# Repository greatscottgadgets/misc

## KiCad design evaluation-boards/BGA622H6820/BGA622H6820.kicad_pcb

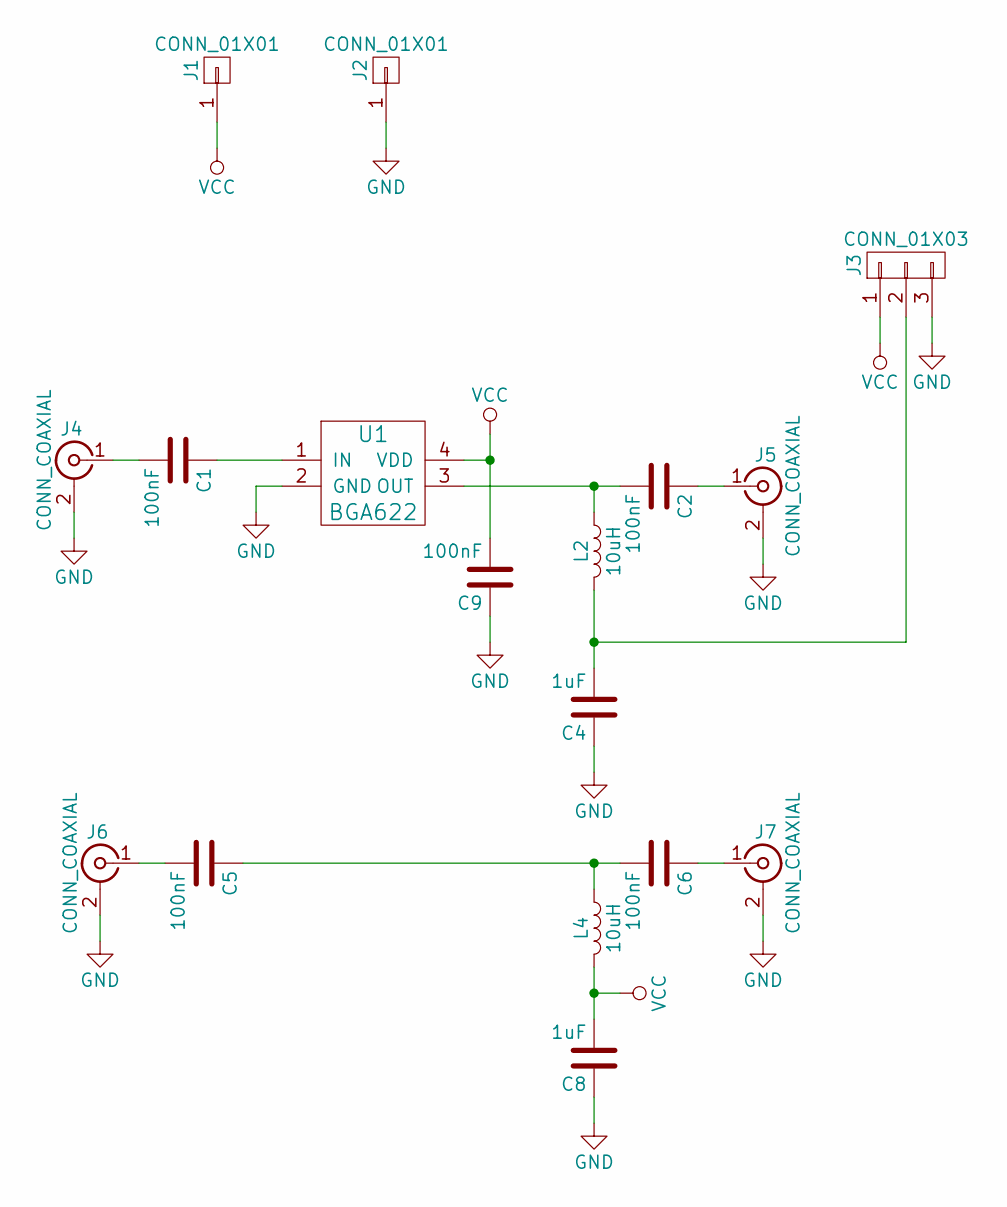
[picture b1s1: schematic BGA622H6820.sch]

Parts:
C1, C2, C5, C6, C9: 100nF; 0402
C4, C8: 1uF; 0603
J1, J2: CONN_01X01; HEADER-1x1
J3: CONN_01X03; HEADER-1x3
J4, J5, J6, J7: CONN_COAXIAL; SMA-VERTICAL
L2, L4: 10uH; 0603
U1: BGA622; SOT343

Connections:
GND: C4.1, C8.1, C9.1, J2.1, J3.3, J4.2 (Ext), J5.2 (Ext), J6.2 (Ext), J7.2 (Ext), U1.2 (GND)
unnamed: C1.1, U1.1 (IN)
unnamed: C1.2, J4.1 (In)
unnamed: C2.1, J5.1 (In)
unnamed: C2.2, L2.1, U1.3 (OUT)
unnamed: C4.2, J3.2, L2.2
unnamed: C5.1, C6.2, L4.1
unnamed: C5.2, J6.1 (In)
unnamed: C6.1, J7.1 (In)
VCC: C8.2, C9.2, J1.1, J3.1, L4.2, U1.4 (VDD)

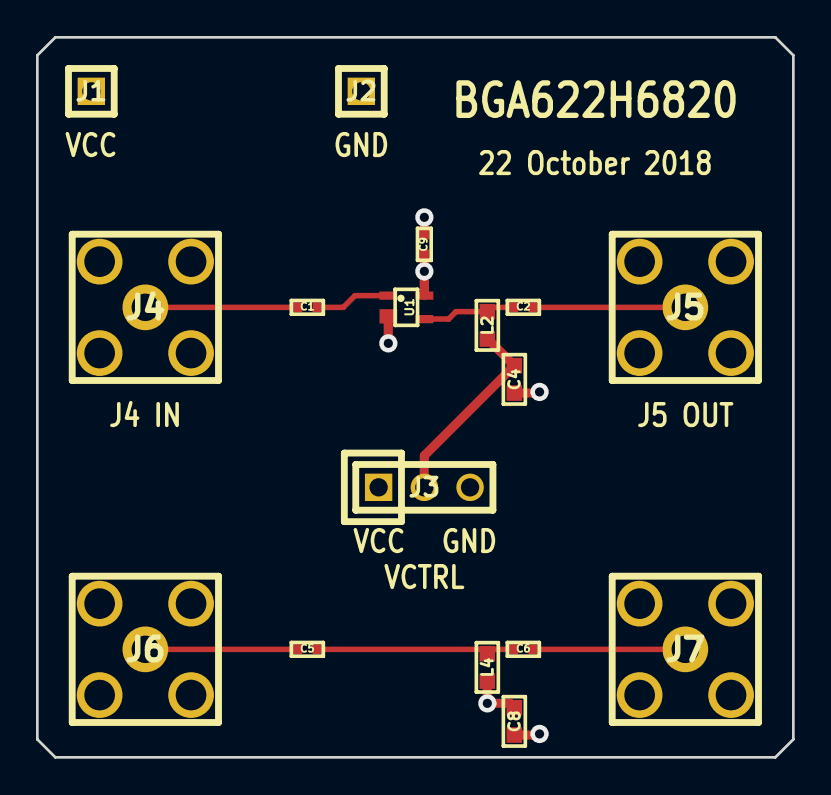
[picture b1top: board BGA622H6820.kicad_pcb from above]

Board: 4 copper layers, 42.0 x 40.0 mm, 17 parts (0 on the bottom side), 10 nets.

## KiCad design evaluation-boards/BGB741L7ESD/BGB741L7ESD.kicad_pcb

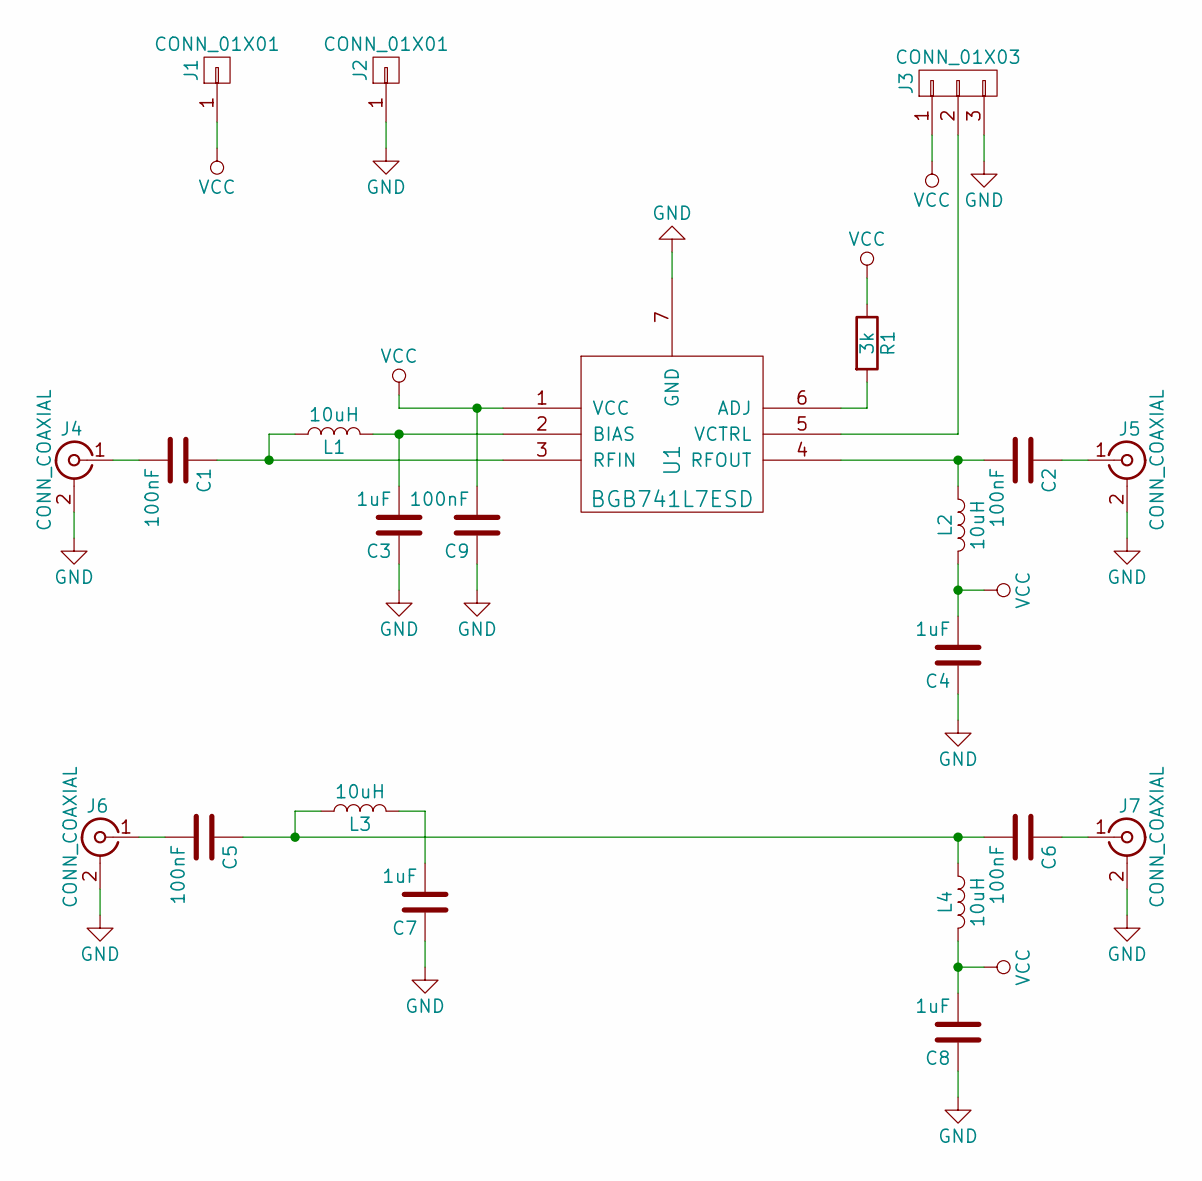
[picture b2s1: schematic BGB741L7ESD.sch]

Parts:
C1, C2, C5, C6, C9: 100nF; 0402
C3, C4, C7, C8: 1uF; 0603
J1, J2: CONN_01X01; HEADER-1x1
J3: CONN_01X03; HEADER-1x3
J4, J5, J6, J7: CONN_COAXIAL; SMA-VERTICAL
L1, L2, L3, L4: 10uH; 0603
R1: 3k; 0603
U1: BGB741L7ESD; TSLP-7-1

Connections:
GND: C3.1, C4.1, C7.1, C8.1, C9.1, J2.1, J3.3, J4.2 (Ext), J5.2 (Ext), J6.2 (Ext), J7.2 (Ext), U1.7 (GND)
unnamed: C1.1, L1.1, U1.3 (RFIN)
unnamed: C1.2, J4.1 (In)
unnamed: C2.1, J5.1 (In)
unnamed: C2.2, L2.1, U1.4 (RFOUT)
unnamed: C3.2, L1.2, U1.2 (BIAS)
unnamed: C5.1, C6.2, L3.1, L4.1
unnamed: C5.2, J6.1 (In)
unnamed: C6.1, J7.1 (In)
unnamed: C7.2, L3.2
unnamed: J3.2, U1.5 (VCTRL)
unnamed: R1.2, U1.6 (ADJ)
VCC: C4.2, C8.2, C9.2, J1.1, J3.1, L2.2, L4.2, R1.1, U1.1 (VCC)

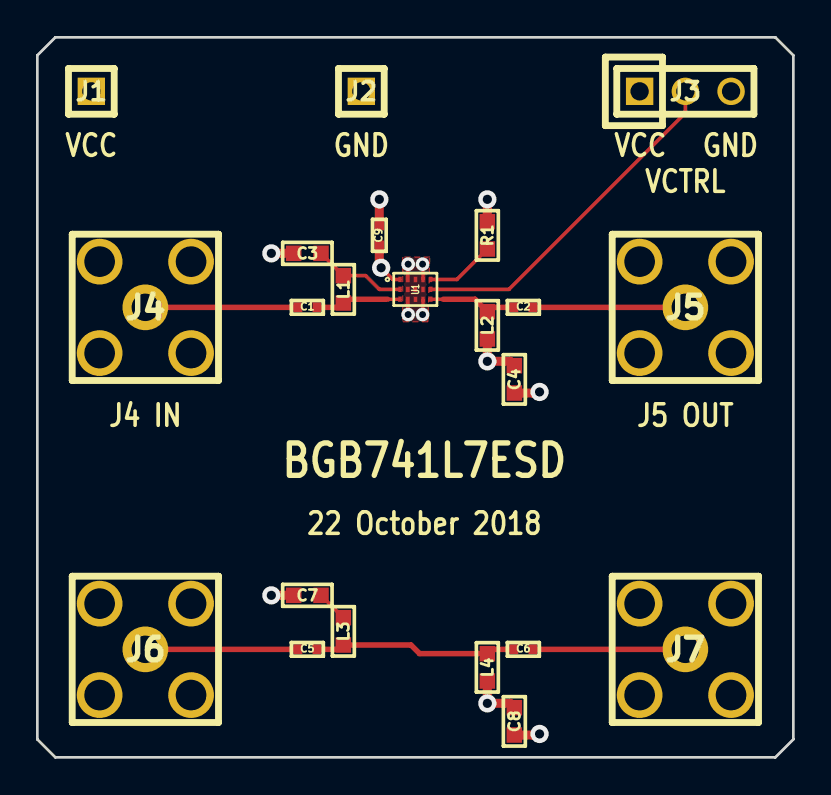
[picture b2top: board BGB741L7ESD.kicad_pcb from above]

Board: 4 copper layers, 42.0 x 40.0 mm, 22 parts (0 on the bottom side), 13 nets.

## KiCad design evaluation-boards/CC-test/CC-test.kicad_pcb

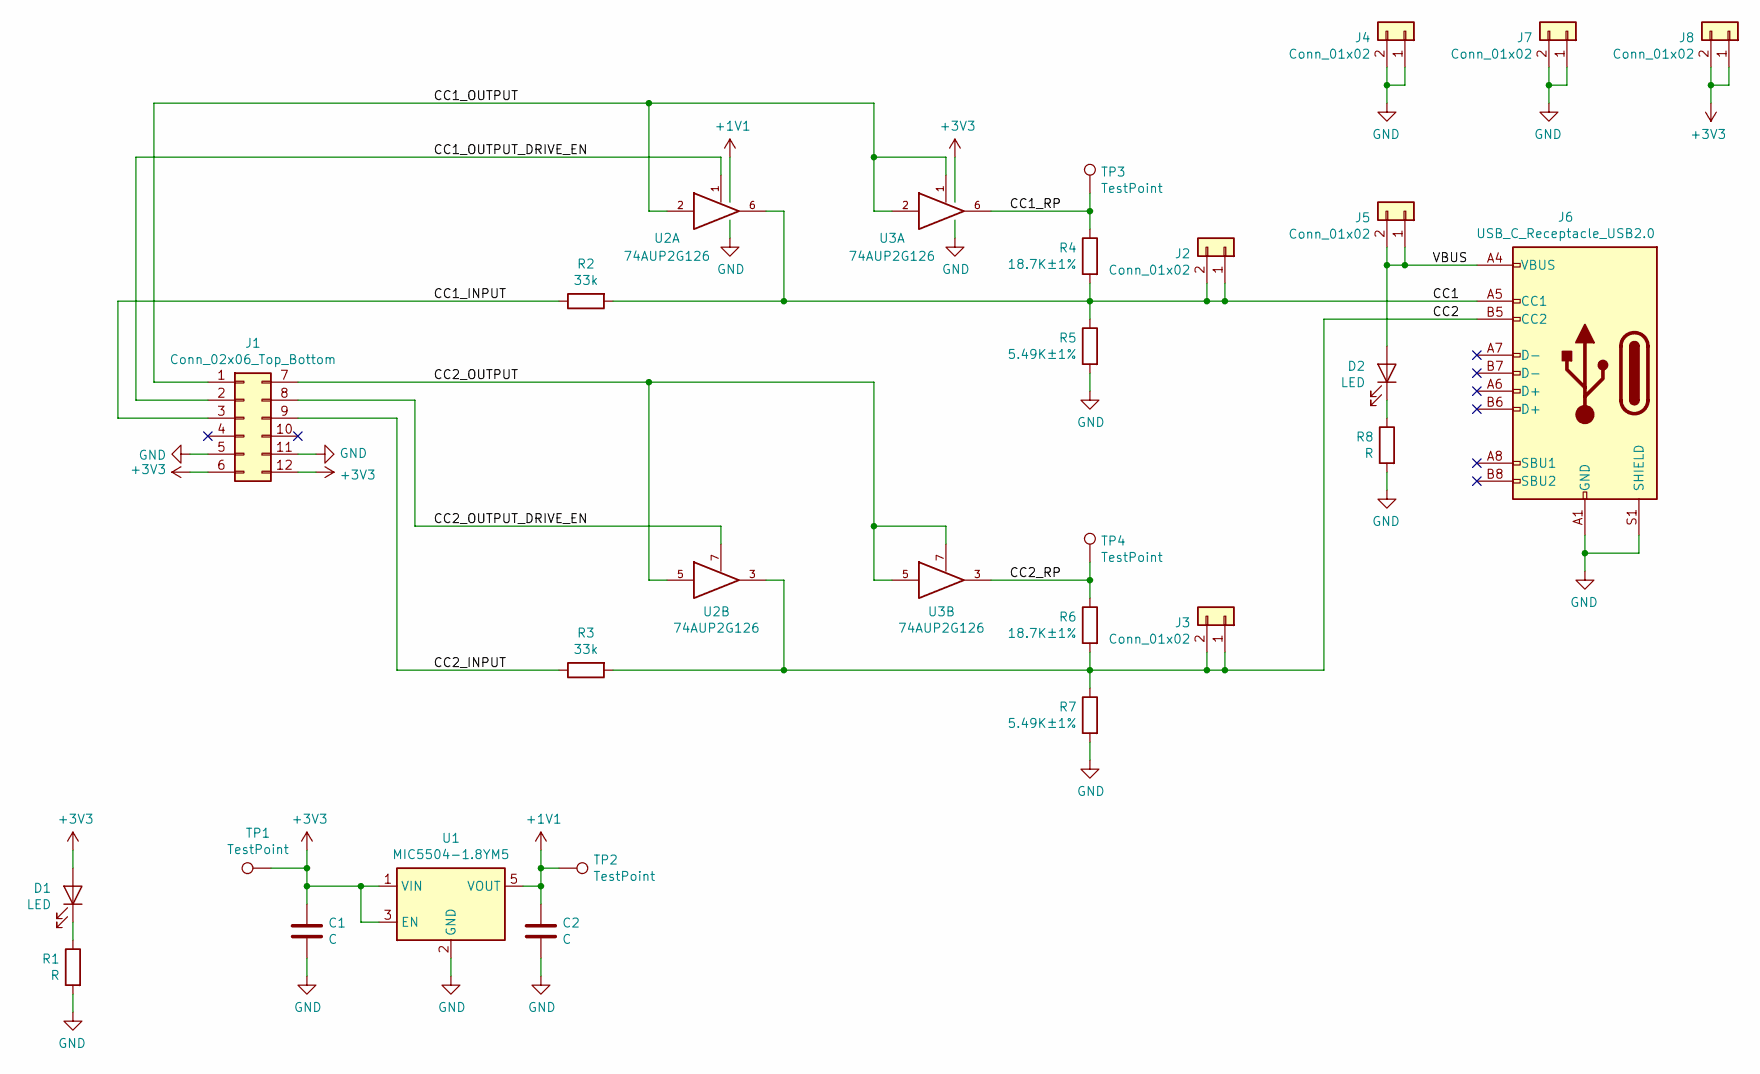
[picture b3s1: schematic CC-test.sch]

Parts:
C1: C; C_0402_1005Metric
C2: C; C_0603_1608Metric
D1, D2: LED; LED_0603_1608Metric_Pad1.05x0.95mm_HandSolder
J1: Conn_02x06_Top_Bottom; PinHeader_2x06_P2.54mm_PMOD
J2, J3, J4, J5, J7, J8: Conn_01x02; PinHeader_1x02_P2.54mm_Vertical
J6: USB_C_Receptacle_USB2.0; USB_C_Receptacle_HRO_TYPE-C-31-M-12
R1, R8: R; R_0402_1005Metric
R2, R3: 33k; R_0402_1005Metric
R4, R6: 18.7K±1%; R_0402_1005Metric
R5, R7: 5.49K±1%; R_0402_1005Metric
TP1, TP2, TP3, TP4: TestPoint; TestPoint_Pad_D1.0mm
U1: MIC5504-1.8YM5; SOT-23-5
U2, U3: 74AUP2G126; X2-DFN1210-8_1.2x1mm_P0.3mm; Part Number 74AUP2G126RA3-7

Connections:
+1V1: C2.1, TP2.1, U1.5 (VOUT), U2.8 (VCC)
+3V3: C1.1, D1.2 (A), J1.6, J1.12, J8.1, J8.2, TP1.1, U1.1 (VIN), U1.3 (EN), U3.8
/CC1: J2.1, J2.2, J6.A5 (CC1), R2.2, R4.2, R5.1, U2.6
/CC1_INPUT: J1.3, R2.1
/CC1_OUTPUT: J1.1, U2.2, U3.1, U3.2
/CC1_OUTPUT_DRIVE_EN: J1.2, U2.1
/CC1_RP: R4.1, TP3.1, U3.6
/CC2: J3.1, J3.2, J6.B5 (CC2), R3.2, R6.2, R7.1, U2.3
/CC2_INPUT: J1.9, R3.1
/CC2_OUTPUT: J1.7, U2.5, U3.5, U3.7
/CC2_OUTPUT_DRIVE_EN: J1.8, U2.7
/CC2_RP: R6.1, TP4.1, U3.3
/VBUS: D2.2 (A), J5.1, J5.2, J6.A4 (VBUS), J6.A9 (VBUS), J6.B4 (VBUS), J6.B9 (VBUS)
GND: C1.2, C2.2, J1.5, J1.11, J4.1, J4.2, J6.A1 (GND), J6.A12 (GND), J6.B1 (GND), J6.B12 (GND), J6.S1 (SHIELD), J7.1, J7.2, R1.2, R5.2, R7.2, R8.2, U1.2 (GND), U2.4 (GND), U3.4 (GND)
unnamed: D1.1 (K), R1.1
unnamed: D2.1 (K), R8.1

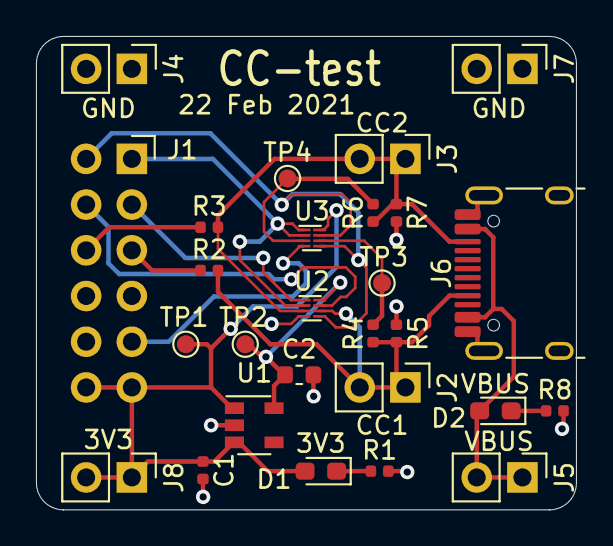
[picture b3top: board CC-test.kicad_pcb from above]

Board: 2 copper layers, 30.0 x 26.3 mm, 27 parts (0 on the bottom side), 16 nets.

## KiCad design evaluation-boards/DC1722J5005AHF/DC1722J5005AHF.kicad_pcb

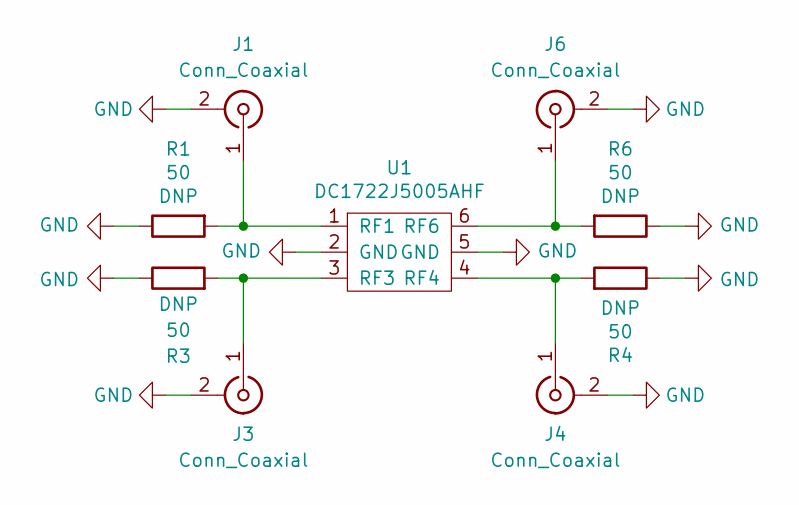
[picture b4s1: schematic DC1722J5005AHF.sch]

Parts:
J1, J3, J4, J6: Conn_Coaxial; SMA-73251-2120
R1, R3, R4, R6: 50; R_0402_1005Metric
U1: DC1722J5005AHF; Anaren_0805_2012Metric-6

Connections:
GND: J1.2 (Ext), J3.2 (Ext), J4.2 (Ext), J6.2 (Ext), R1.1, R3.1, R4.1, R6.1, U1.2 (GND), U1.5 (GND)
unnamed: J1.1 (In), R1.2, U1.1 (RF1)
unnamed: J3.1 (In), R3.2, U1.3 (RF3)
unnamed: J4.1 (In), R4.2, U1.4 (RF4)
unnamed: J6.1 (In), R6.2, U1.6 (RF6)

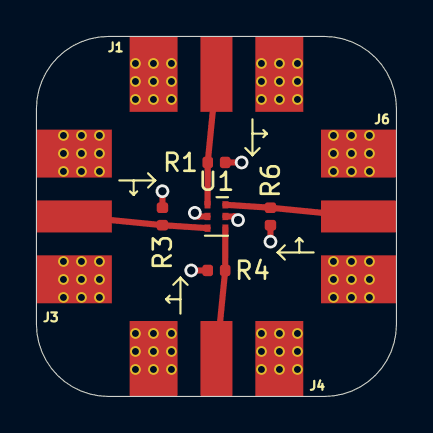
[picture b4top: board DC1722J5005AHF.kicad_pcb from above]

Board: 4 copper layers, 20.0 x 20.0 mm, 9 parts (0 on the bottom side), 5 nets.

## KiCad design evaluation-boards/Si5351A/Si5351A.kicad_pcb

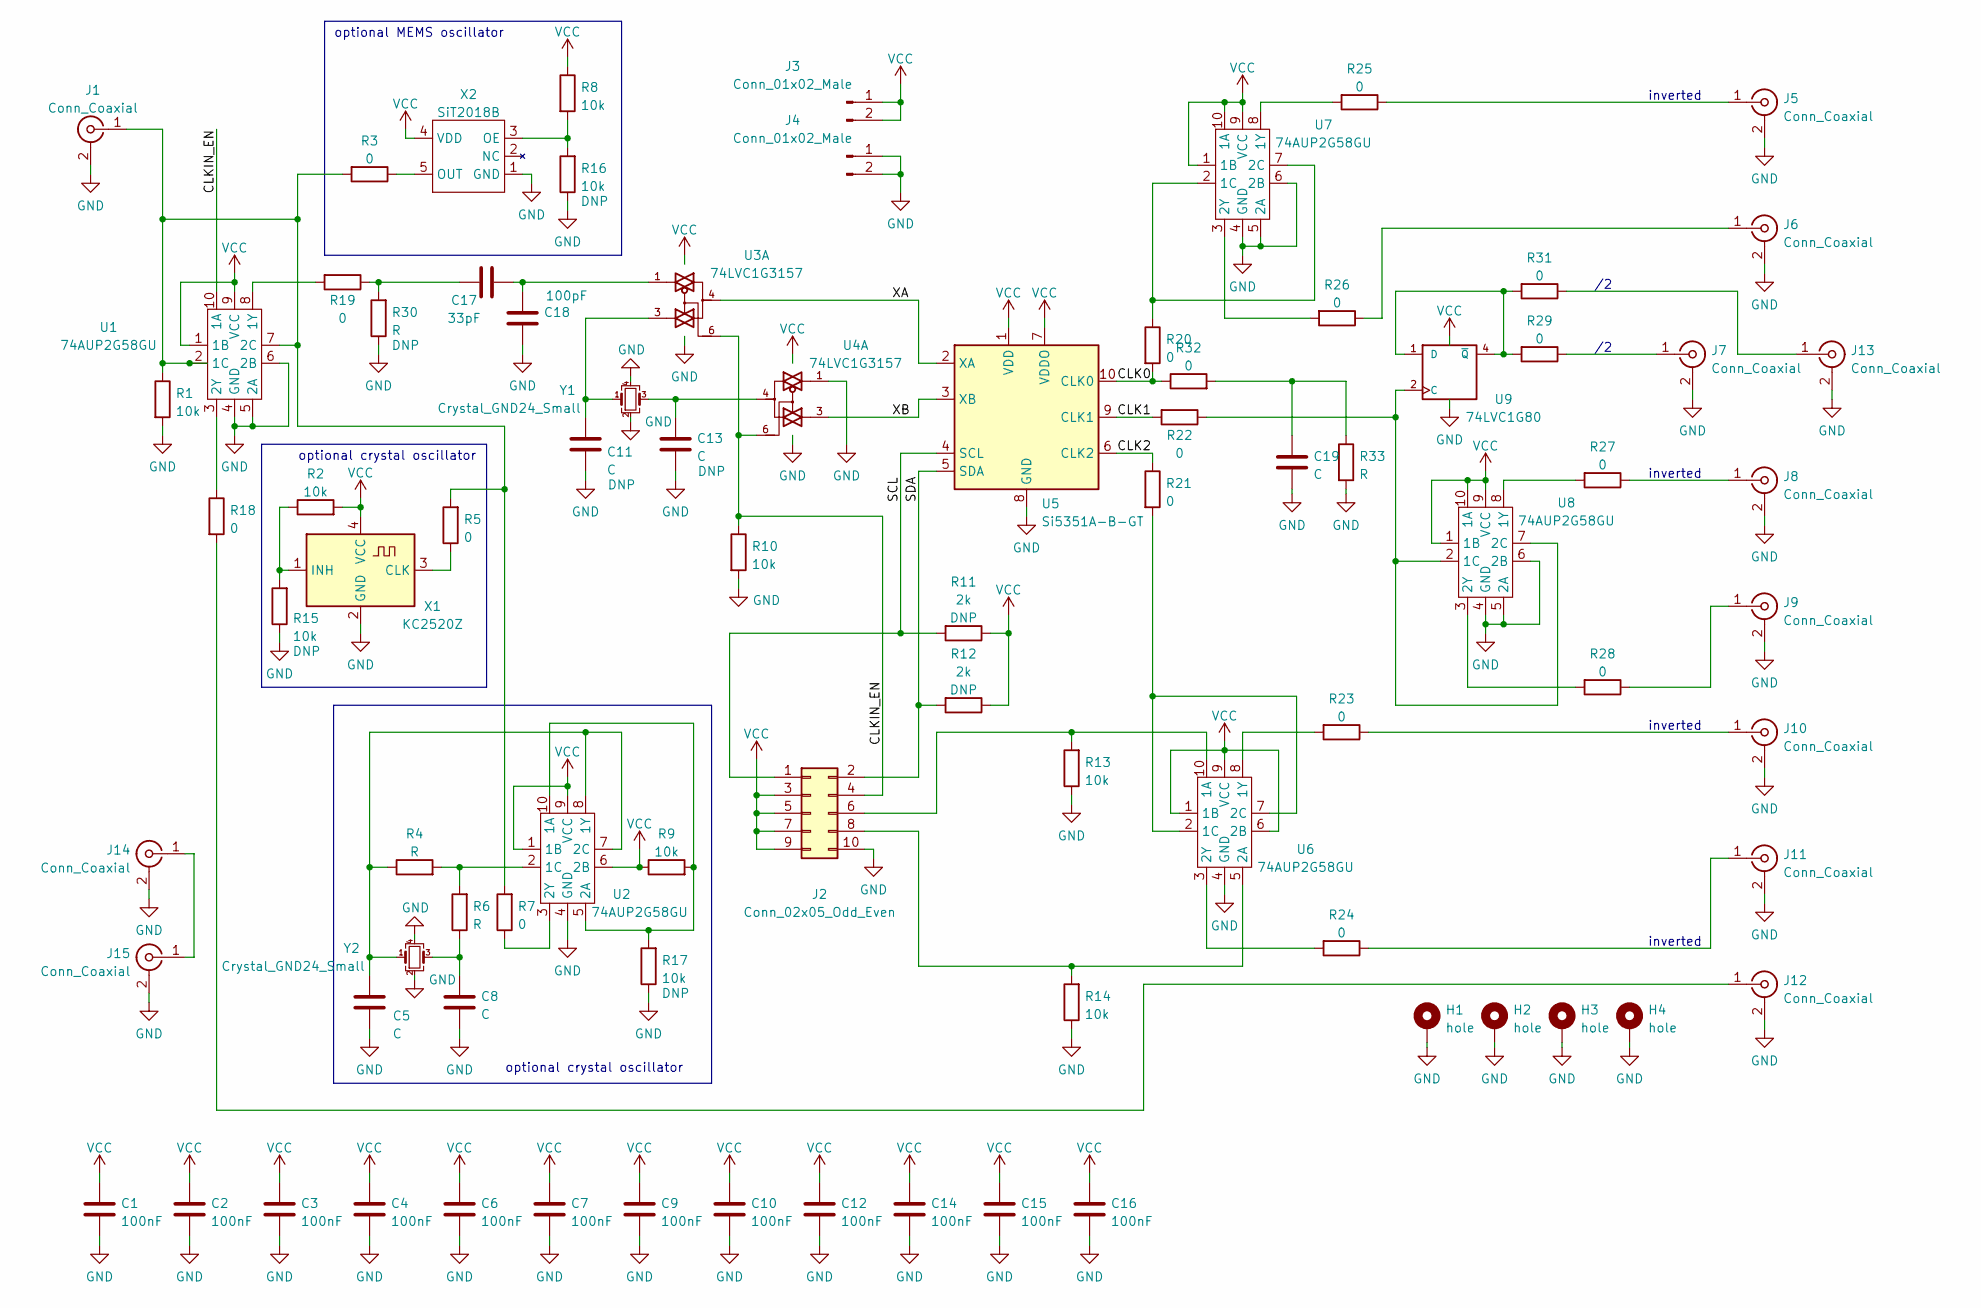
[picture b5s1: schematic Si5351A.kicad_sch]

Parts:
C1, C2, C3, C4, C6, C7, C9, C10, C12, C14, C15, C16: 100nF; C_0402_1005Metric
C5, C8, C11, C13, C19: C; C_0402_1005Metric
C17: 33pF; C_0402_1005Metric
C18: 100pF; C_0402_1005Metric
H1, H2, H3, H4: hole; MountingHole_2.2mm_M2_Pad_Via
J1, J5, J6, J7, J8, J9, J10, J11, J12, J13, J14, J15: Conn_Coaxial; SMA-EDGE
J2: Conn_02x05_Odd_Even; PinHeader_2x05_P2.54mm_Vertical
J3, J4: Conn_01x02_Male; PinHeader_1x02_P2.54mm_Vertical
R1, R2, R8, R9, R10, R13, R14, R15, R16, R17: 10k; R_0402_1005Metric
R3, R5, R7, R18, R19, R20, R21, R22, R23, R24, R25, R26, R27, R28, R29, R31, R32: 0; R_0402_1005Metric
R4, R6, R30, R33: R; R_0402_1005Metric
R11, R12: 2k; R_0402_1005Metric
U1, U2, U6, U7, U8: 74AUP2G58GU; XQFN10; Part Number 74AUP2G58GUX
U3, U4: 74LVC1G3157; XSON6; Part Number 74LVC1G3157GM,115
U5: Si5351A-B-GT; MSOP-10_3x3mm_P0.5mm; Part Number Si5351A-B-GTR
U9: 74LVC1G80; SOT-353_SC-70-5; Part Number SN74LVC1G80DCKR
X1: KC2520Z; Oscillator_SMD_Kyocera_KC2520Z-4Pin_2.5x2.0mm; Part Number KC2520Z25.0000C1KX00
X2: SiT2018B; SOT-23-5; Part Number SIT2018BEAS1-33N-27.000000E
Y1, Y2: Crystal_GND24_Small; Crystal_SMD_3225-4Pin_3.2x2.5mm

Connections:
/CLK0: R20.2, R32.1, U5.10 (CLK0)
/CLK1: R22.2, U5.9 (CLK1)
/CLK2: R21.1, U5.6 (CLK2)
/CLKIN_EN: J2.4, R10.1, U1.10 (1A), U3.6, U4.6
/SCL: J2.1, R11.2, U5.4 (SCL)
/SDA: J2.2, R12.2, U5.5 (SDA)
/XA: U3.4, U5.2 (XA)
/XB: U4.3, U5.3 (XB)
GND: C1.2, C2.2, C3.2, C4.2, C5.2, C6.2, C7.2, C8.2, C9.2, C10.2, C11.2, C12.2, C13.2, C14.2, C15.2, C16.2, C18.2, C19.2, H1.1, H2.1, H3.1, H4.1, J1.2 (Ext), J2.10, J4.1, J4.2, J5.2 (Ext), J6.2 (Ext), J7.2 (Ext), J8.2 (Ext), J9.2 (Ext), J10.2 (Ext), J11.2 (Ext), J12.2 (Ext), J13.2 (Ext), J14.2 (Ext), J15.2 (Ext), R1.2, R10.2, R13.1, R14.1, R15.1, R16.1, R17.1, R30.1, R33.2, U1.4 (GND), U1.5 (2A), U1.6 (2B), U2.4 (GND), U3.2 (GND), U4.1, U4.2 (GND), U5.8 (GND), U6.4 (GND), U7.4 (GND), U7.5 (2A), U7.6 (2B), U8.4 (GND), U8.5 (2A), U8.6 (2B), U9.3 (GND), X1.2 (GND), X2.1 (GND), Y1.2, Y1.4, Y2.2, Y2.4
unnamed: C5.1, R4.1, U2.7 (2C), U2.8 (1Y), Y2.1
unnamed: C8.1, R6.1, Y2.3
unnamed: C11.1, U3.3, Y1.1
unnamed: C13.1, U4.4, Y1.3
unnamed: C17.1, R19.1, R30.2
unnamed: C17.2, C18.1, U3.1
unnamed: C19.1, R32.2, R33.1
unnamed: J1.1 (In), R1.1, R3.2, R5.2, R7.2, U1.2 (1C), U1.7 (2C)
unnamed: J2.6, R13.2, U6.10 (1A)
unnamed: J2.8, R14.2, U6.5 (2A)
unnamed: J5.1 (In), R25.1
unnamed: J6.1 (In), R26.1
unnamed: J7.1 (In), R29.1
unnamed: J8.1 (In), R27.1
unnamed: J9.1 (In), R28.1
unnamed: J10.1 (In), R23.1
unnamed: J11.1 (In), R24.1
unnamed: J12.1 (In), R18.2
unnamed: J13.1 (In), R31.1
unnamed: J14.1 (In), J15.1 (In)
unnamed: R3.1, X2.5 (OUT)
unnamed: R4.2, R6.2, U2.2 (1C)
unnamed: R5.1, X1.3 (CLK)
unnamed: R7.1, U2.3 (2Y)
unnamed: R2.1, R15.2, X1.1 (INH)
unnamed: R8.2, R16.2, X2.3 (OE)
unnamed: R9.2, R17.2, U2.5 (2A), U2.10 (1A)
unnamed: R18.1, U1.3 (2Y)
unnamed: R19.2, U1.8 (1Y)
unnamed: R20.1, U7.2 (1C), U7.7 (2C)
unnamed: R21.2, U6.2 (1C), U6.7 (2C)
unnamed: R22.1, U8.2 (1C), U8.7 (2C), U9.2 (C)
unnamed: R23.2, U6.8 (1Y)
unnamed: R24.2, U6.3 (2Y)
unnamed: R25.2, U7.8 (1Y)
unnamed: R26.2, U7.3 (2Y)
unnamed: R27.2, U8.8 (1Y)
unnamed: R28.2, U8.3 (2Y)
unnamed: R29.2, R31.2, U9.1 (D), U9.4 (~Q)
VCC: C1.1, C2.1, C3.1, C4.1, C6.1, C7.1, C9.1, C10.1, C12.1, C14.1, C15.1, C16.1, J2.3, J2.5, J2.7, J2.9, J3.1, J3.2, R2.2, R8.1, R9.1, R11.1, R12.1, U1.1 (1B), U1.9 (VCC), U2.1 (1B), U2.6 (2B), U2.9 (VCC), U3.5 (VCC), U4.5 (VCC), U5.1 (VDD), U5.7 (VDDO), U6.1 (1B), U6.6 (2B), U6.9 (VCC), U7.1 (1B), U7.9 (VCC), U7.10 (1A), U8.1 (1B), U8.9 (VCC), U8.10 (1A), U9.5 (VCC), X1.4 (VCC), X2.4 (VDD)

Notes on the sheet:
inverted
optional MEMS oscillator
optional crystal oscillator

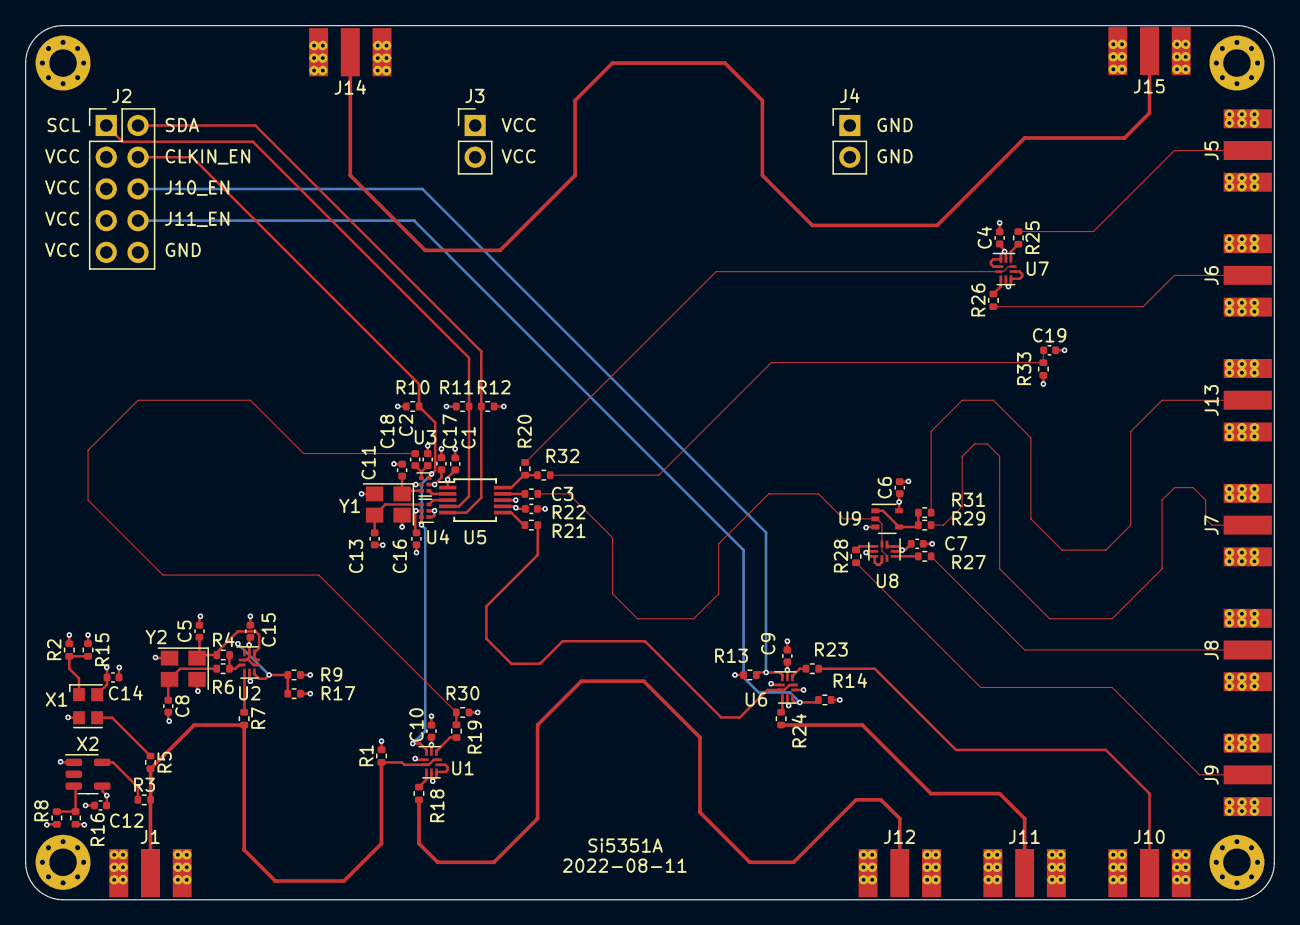
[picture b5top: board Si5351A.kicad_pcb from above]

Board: 4 copper layers, 100.0 x 70.0 mm, 84 parts (0 on the bottom side), 49 nets.

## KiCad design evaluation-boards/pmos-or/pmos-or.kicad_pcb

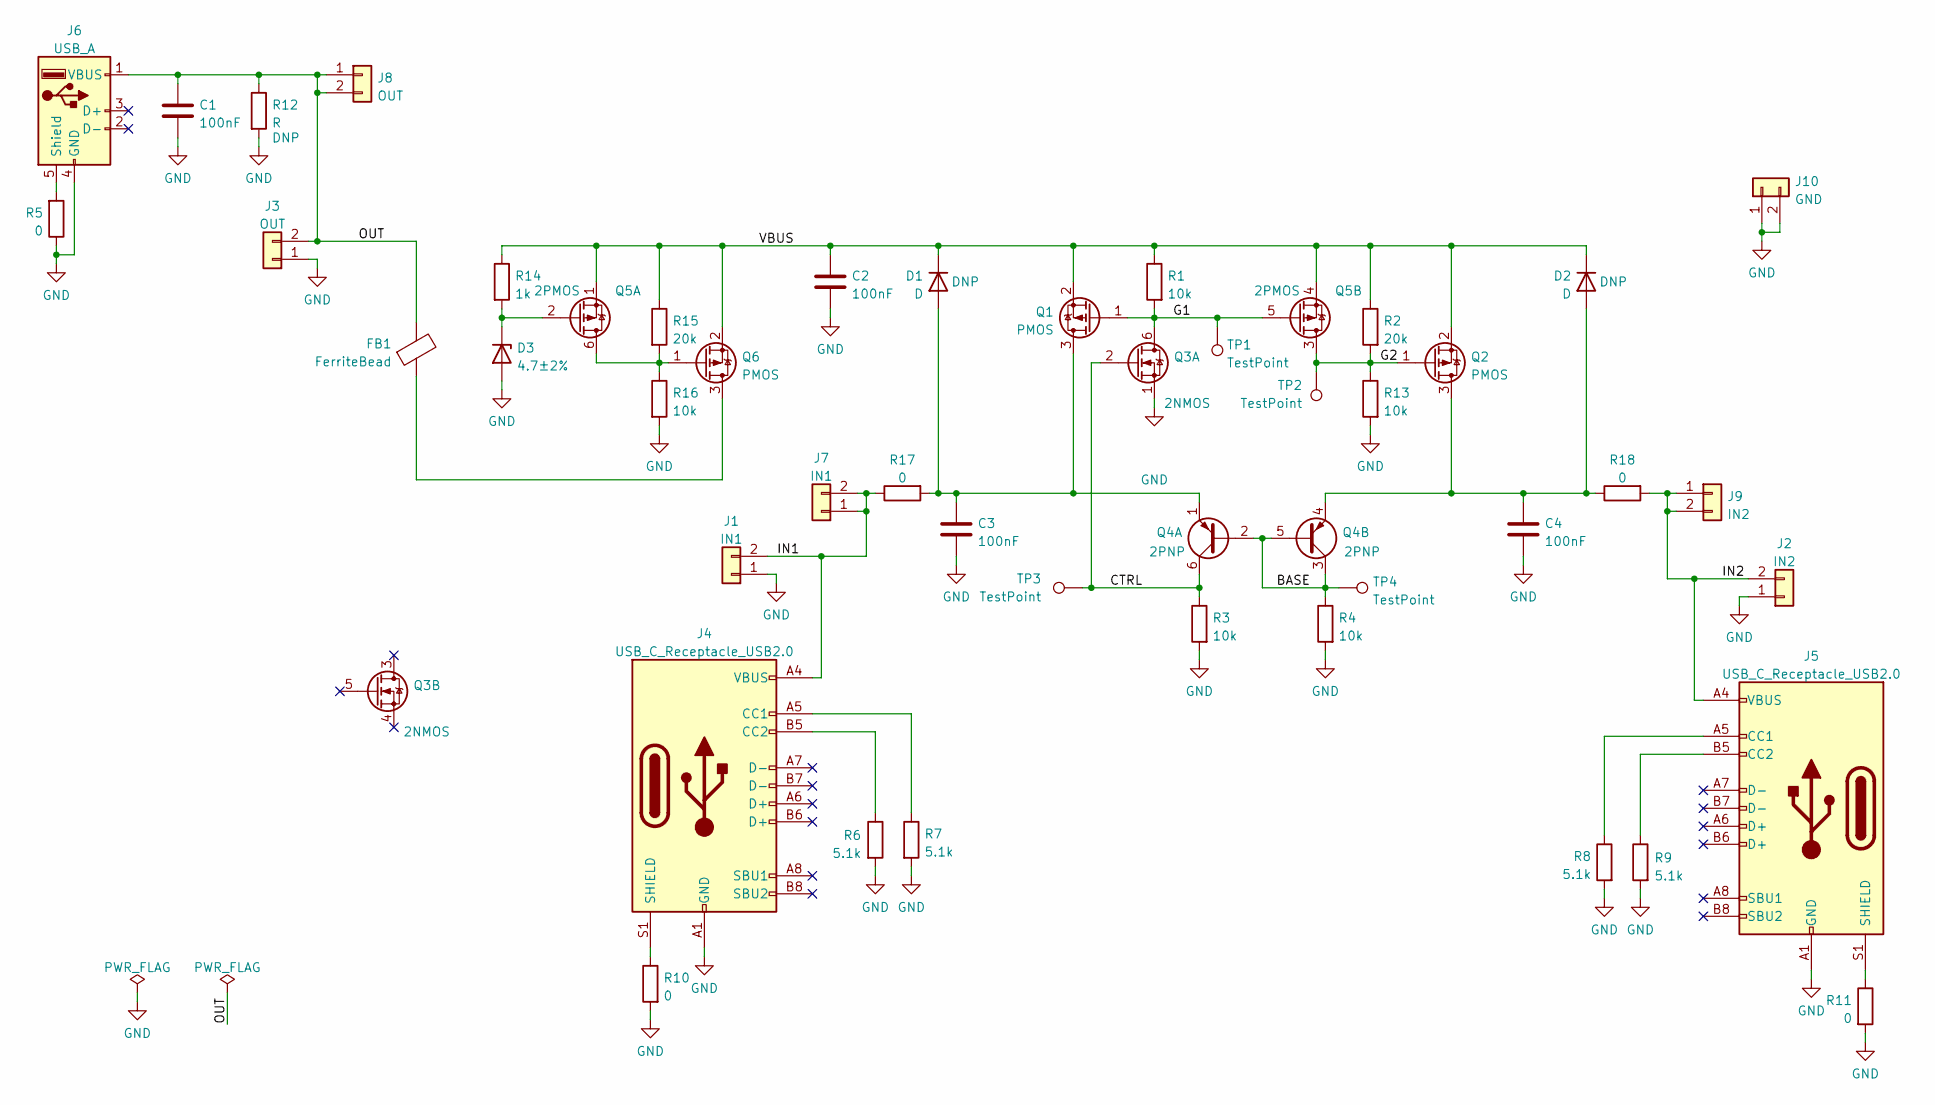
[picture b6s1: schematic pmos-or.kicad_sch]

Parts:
C1, C2, C3, C4: 100nF; C_0402_1005Metric
D1, D2: D; SOD128; Part Number PMEG3050BEP,115
D3: 4.7±2%; DFN1006-2; Part Number BZX884-B4V7,315
FB1: FerriteBead; L_0805_2012Metric
J1: IN1; Banana_Jack_2Pin
J2: IN2; Banana_Jack_2Pin
J3: OUT; Banana_Jack_2Pin
J4, J5: USB_C_Receptacle_USB2.0; USB_C_Receptacle_HRO_TYPE-C-31-M-12; Part Number U262-161N-4BVC11
J6: USB_A; USB_A_Kycon_KUSBXHT-SB-AS1N-B30-NF_Horizontal; Part Number C42411
J7: IN1; PinHeader_1x02_P2.54mm_Vertical
J8: OUT; PinHeader_1x02_P2.54mm_Vertical
J9: IN2; PinHeader_1x02_P2.54mm_Vertical
J10: GND; PinHeader_1x02_P2.54mm_Vertical
Q1, Q2, Q6: PMOS; SOT-23-3; Part Number PJA3441_R1_00001
Q3: 2NMOS; SOT-363_SC-70-6; Part Number 2N7002DW
Q4: 2PNP; SOT-363_SC-70-6; Part Number BCM857BS-7-F
Q5: 2PMOS; SOT-363_SC-70-6; Part Number BSS84DW
R1, R3, R4, R13, R16: 10k; R_0402_1005Metric
R2, R15: 20k; R_0402_1005Metric
R5, R10, R11, R17, R18: 0; R_0402_1005Metric
R6, R7, R8, R9: 5.1k; R_0402_1005Metric
R12: R; R_0402_1005Metric
R14: 1k; R_0402_1005Metric
TP1, TP2, TP3, TP4: TestPoint; TestPoint_Pad_D2.0mm

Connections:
/BASE: Q4.2 (B1), Q4.3 (C2), Q4.5 (B2), R4.1, TP4.1
/CTRL: Q3.2 (G), Q4.6 (C1), R3.1, TP3.1
/G1: Q1.1 (G), Q3.6 (D), Q5.5 (G), R1.2, TP1.1
/G2: Q2.1 (G), Q5.3 (D), R2.2, R13.1, TP2.1
/IN1: J1.2, J4.A4 (VBUS), J4.A9 (VBUS), J4.B4 (VBUS), J4.B9 (VBUS), J7.1, J7.2, R17.1
/IN2: J2.2, J5.A4 (VBUS), J5.A9 (VBUS), J5.B4 (VBUS), J5.B9 (VBUS), J9.1, J9.2, R18.2
/OUT: C1.1, FB1.2, J3.2, J6.1 (VBUS), J8.1, J8.2, R12.1
/VBUS: C2.1, D1.1 (K), D2.1 (K), Q1.2 (S), Q2.2 (S), Q5.1 (S), Q5.4 (S), Q6.2 (S), R1.1, R2.1, R14.1, R15.1
GND: C1.2, C2.2, C3.2, C4.2, D3.2 (A), J1.1, J2.1, J3.1, J4.A1 (GND), J4.A12 (GND), J4.B1 (GND), J4.B12 (GND), J5.A1 (GND), J5.A12 (GND), J5.B1 (GND), J5.B12 (GND), J6.4 (GND), J10.1, J10.2, Q3.1 (S), R3.2, R4.2, R5.1, R6.2, R7.2, R8.2, R9.2, R10.2, R11.2, R12.2, R13.2, R16.2
unnamed: C3.1, D1.2 (A), Q1.3 (D), Q4.1 (E1), R17.2
unnamed: C4.1, D2.2 (A), Q2.3 (D), Q4.4 (E2), R18.1
unnamed: D3.1 (K), Q5.2 (G), R14.2
unnamed: FB1.1, Q6.3 (D)
unnamed: J4.A5 (CC1), R7.1
unnamed: J4.B5 (CC2), R6.1
unnamed: J4.S1 (SHIELD), R10.1
unnamed: J5.A5 (CC1), R8.1
unnamed: J5.B5 (CC2), R9.1
unnamed: J5.S1 (SHIELD), R11.1
unnamed: J6.5 (Shield), R5.2
unnamed: Q5.6 (D), Q6.1 (G), R15.2, R16.1

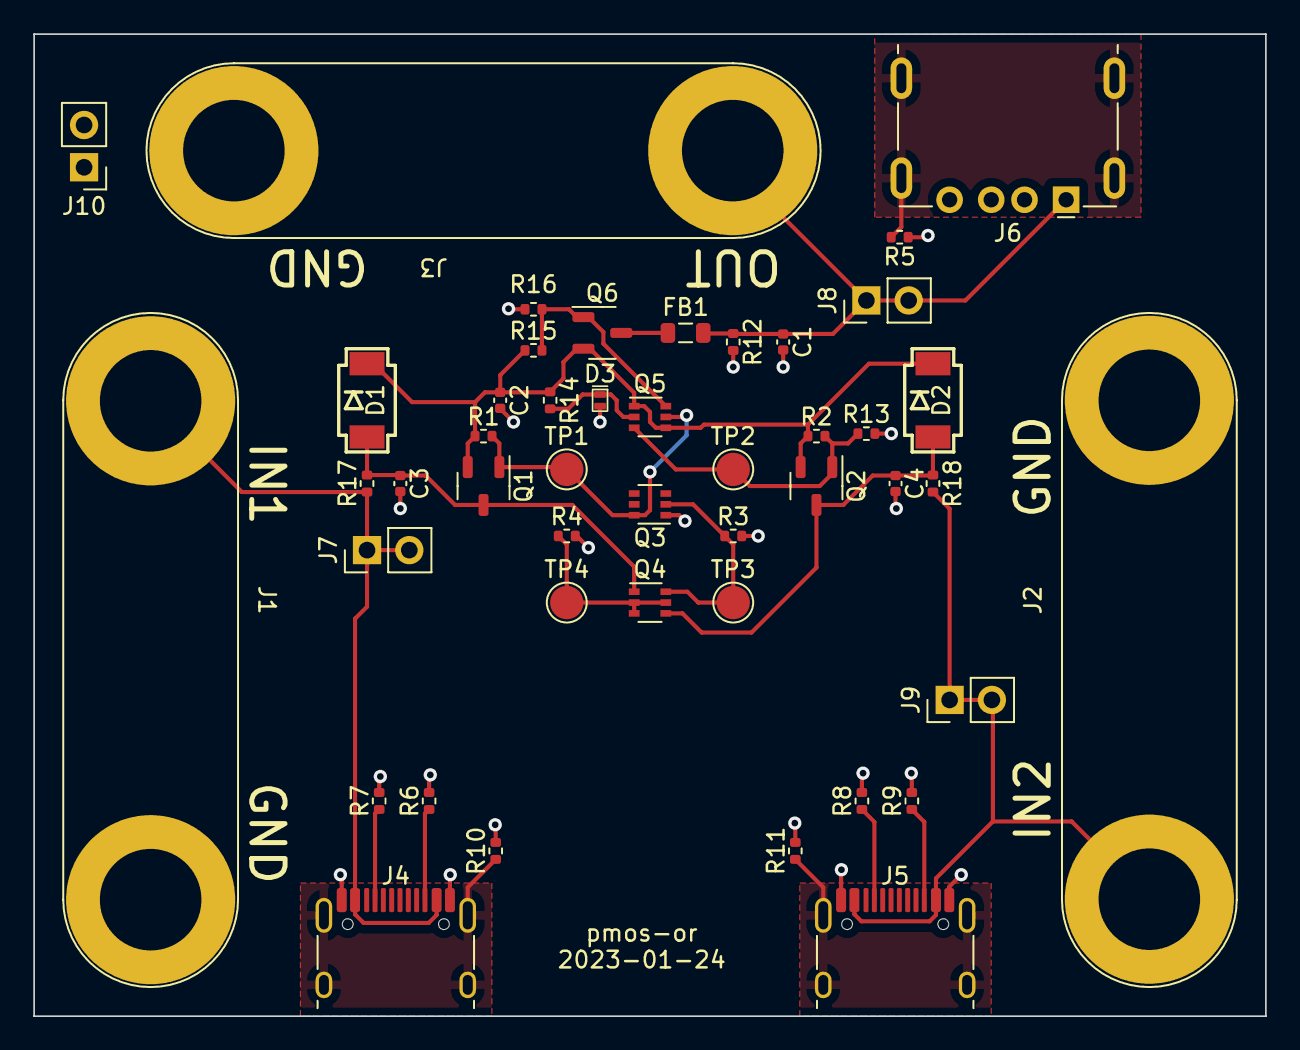
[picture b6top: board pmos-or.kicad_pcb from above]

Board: 2 copper layers, 74.0 x 59.0 mm, 46 parts (0 on the bottom side), 21 nets.

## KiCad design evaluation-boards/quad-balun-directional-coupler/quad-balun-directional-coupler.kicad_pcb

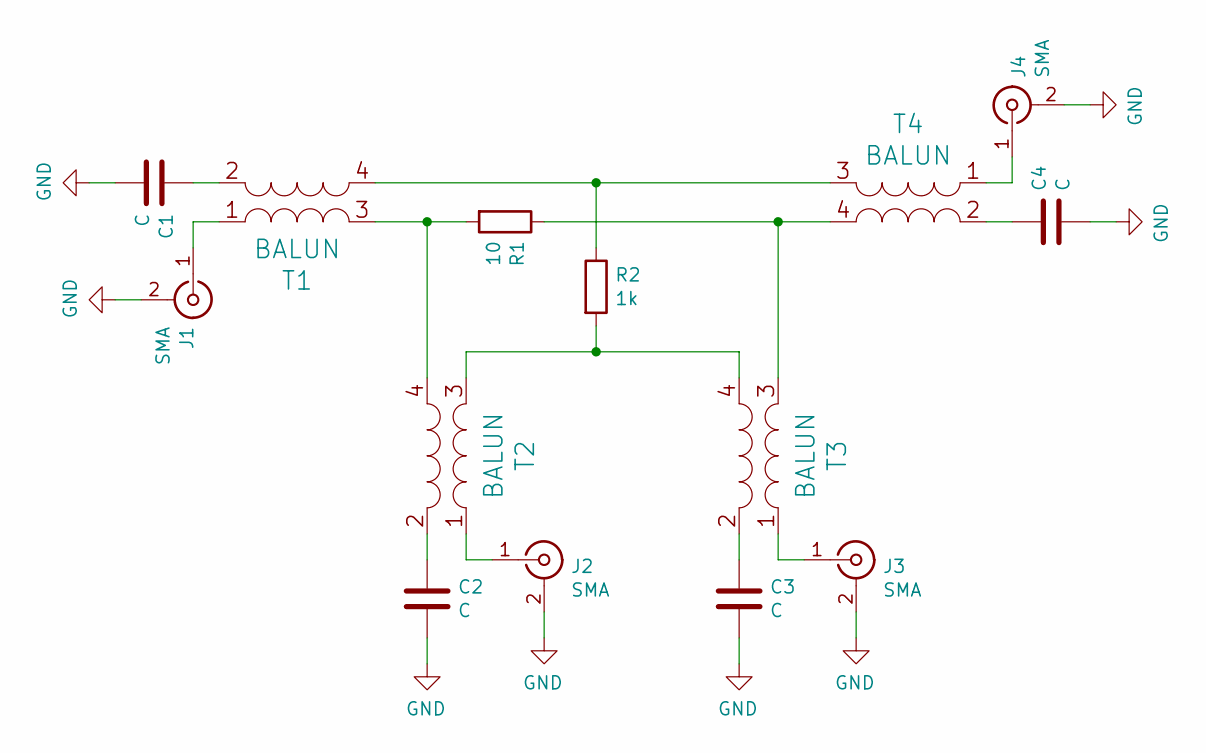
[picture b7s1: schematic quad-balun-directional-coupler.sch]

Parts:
C1, C2, C3, C4: C; 0402
J1, J2, J3, J4: SMA; SMA-73251-2120
R1: 10; 0402
R2: 1k; 0402
T1, T2, T3, T4: BALUN; Anaren_0805_2012Metric-6; Part Number B0322J5050AHF

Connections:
GND: C1.2, C2.2, C3.2, C4.2, J1.2 (Ext), J2.2 (Ext), J3.2 (Ext), J4.2 (Ext)
unnamed: C1.1, T1.2 (S2)
unnamed: C2.1, T2.2 (S2)
unnamed: C3.1, T3.2 (S2)
unnamed: C4.1, T4.2 (S2)
unnamed: J1.1 (In), T1.1 (S1)
unnamed: J2.1 (In), T2.1 (S1)
unnamed: J3.1 (In), T3.1 (S1)
unnamed: J4.1 (In), T4.1 (S1)
unnamed: R1.1, T3.3 (PR1), T4.4 (PR2)
unnamed: R1.2, T1.3 (PR1), T2.4 (PR2)
unnamed: R2.1, T1.4 (PR2), T4.3 (PR1)
unnamed: R2.2, T2.3 (PR1), T3.4 (PR2)

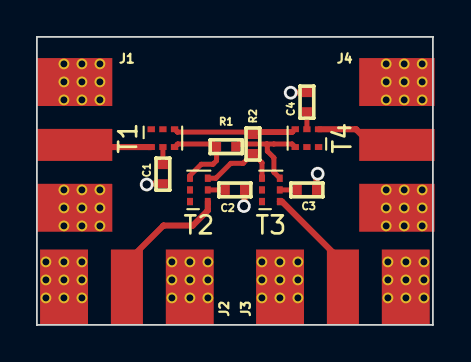
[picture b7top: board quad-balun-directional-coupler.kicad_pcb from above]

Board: 4 copper layers, 22.0 x 16.0 mm, 14 parts (0 on the bottom side), 13 nets.

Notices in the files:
parts and their libraries:
COPYRIGHT: Copyright 2023 Great Scott Gadgets
LICENSE: Licensed under the CERN-OHL-P v2
